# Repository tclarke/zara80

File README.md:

# zara80
A retro computer based on the Z80 and STEbus

See [the hackaday project](https://hackaday.io/project/190621-zara80) for details.

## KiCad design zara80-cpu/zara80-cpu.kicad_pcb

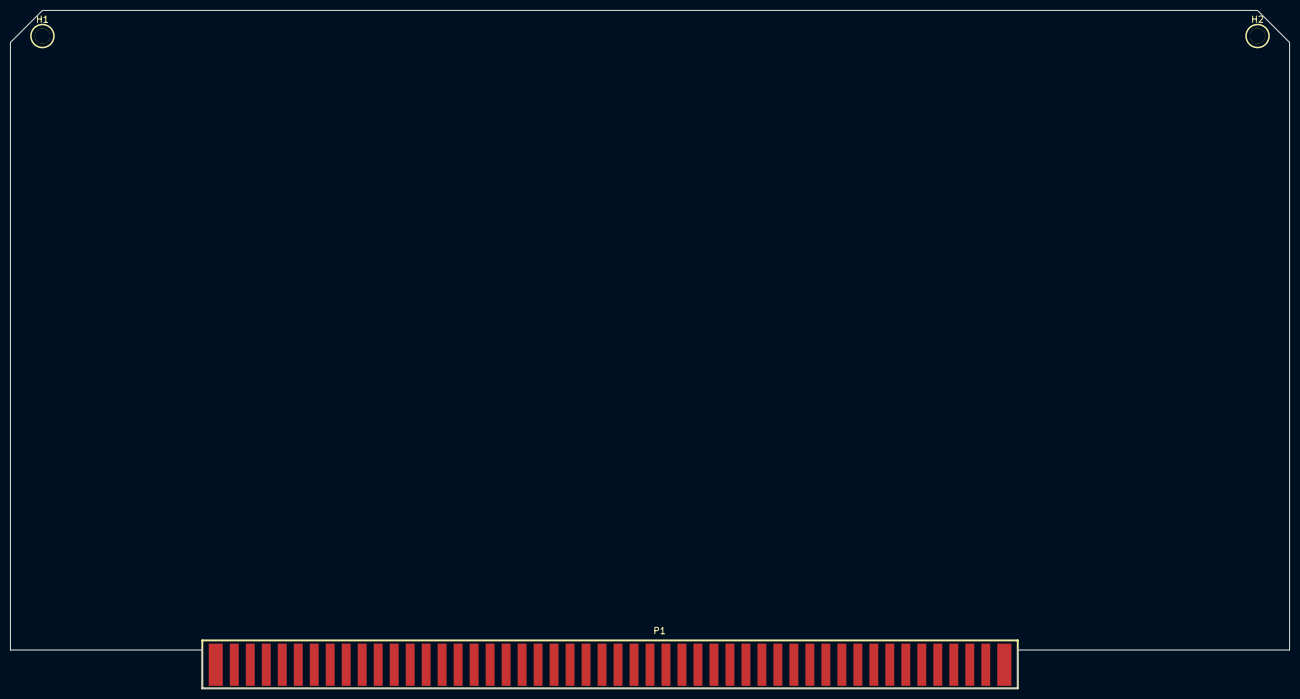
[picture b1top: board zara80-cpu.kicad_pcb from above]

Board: 2 copper layers, 254.0 x 134.6 mm, 3 parts (0 on the bottom side), 2 nets, no tracks yet.

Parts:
H1, H2: Ejector; s100-ejector
P1: S100_MALE

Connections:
/0V: P1.50, P1.100
/+8V: P1.1, P1.51

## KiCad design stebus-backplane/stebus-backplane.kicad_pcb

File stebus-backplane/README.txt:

This is a STEbus backplane with 5 slots and active termination.

It uses an ATX power supply and has options to enable or short
the soft power button for the supply. It can also connect the ATX
+5VSB line to the VSTBY pin on the bus. This allows you to simulate
and test power failures by powering off the soft power button. The VSTBY
acts as a +5V battery. If disabled it connects VSTBY to the normal +5v.

There are no power indicator LEDs since the power supply will typically have
these already.

The active termination uses the sample circuit from the STEbus Standards document.

stebus-backplane.v1.pcbway.gerbers.zip contains the gerbers used to order rev 1
of the board from PCBway who kindly provided free manufacture as a sponsorship
for rev 1.

Most of the parts can be substituted for similar parts. Resistors should be
approximately the same but most can be a few percent off. The (rev 2 and
newer) 2.8v regulator should work fine with any pin compatible regulator. It's
used as a pullup in the termination circuit so it shouldn't pull much current
and the footprint is pretty standard for 2 pin SMD regulators. The DIN
connectors are meant to be interchangable with any DIN41612. They are 2x32 pin
female AC connectors. The Molex is a standard 24-pin ATX connector so other
brands should work fine.

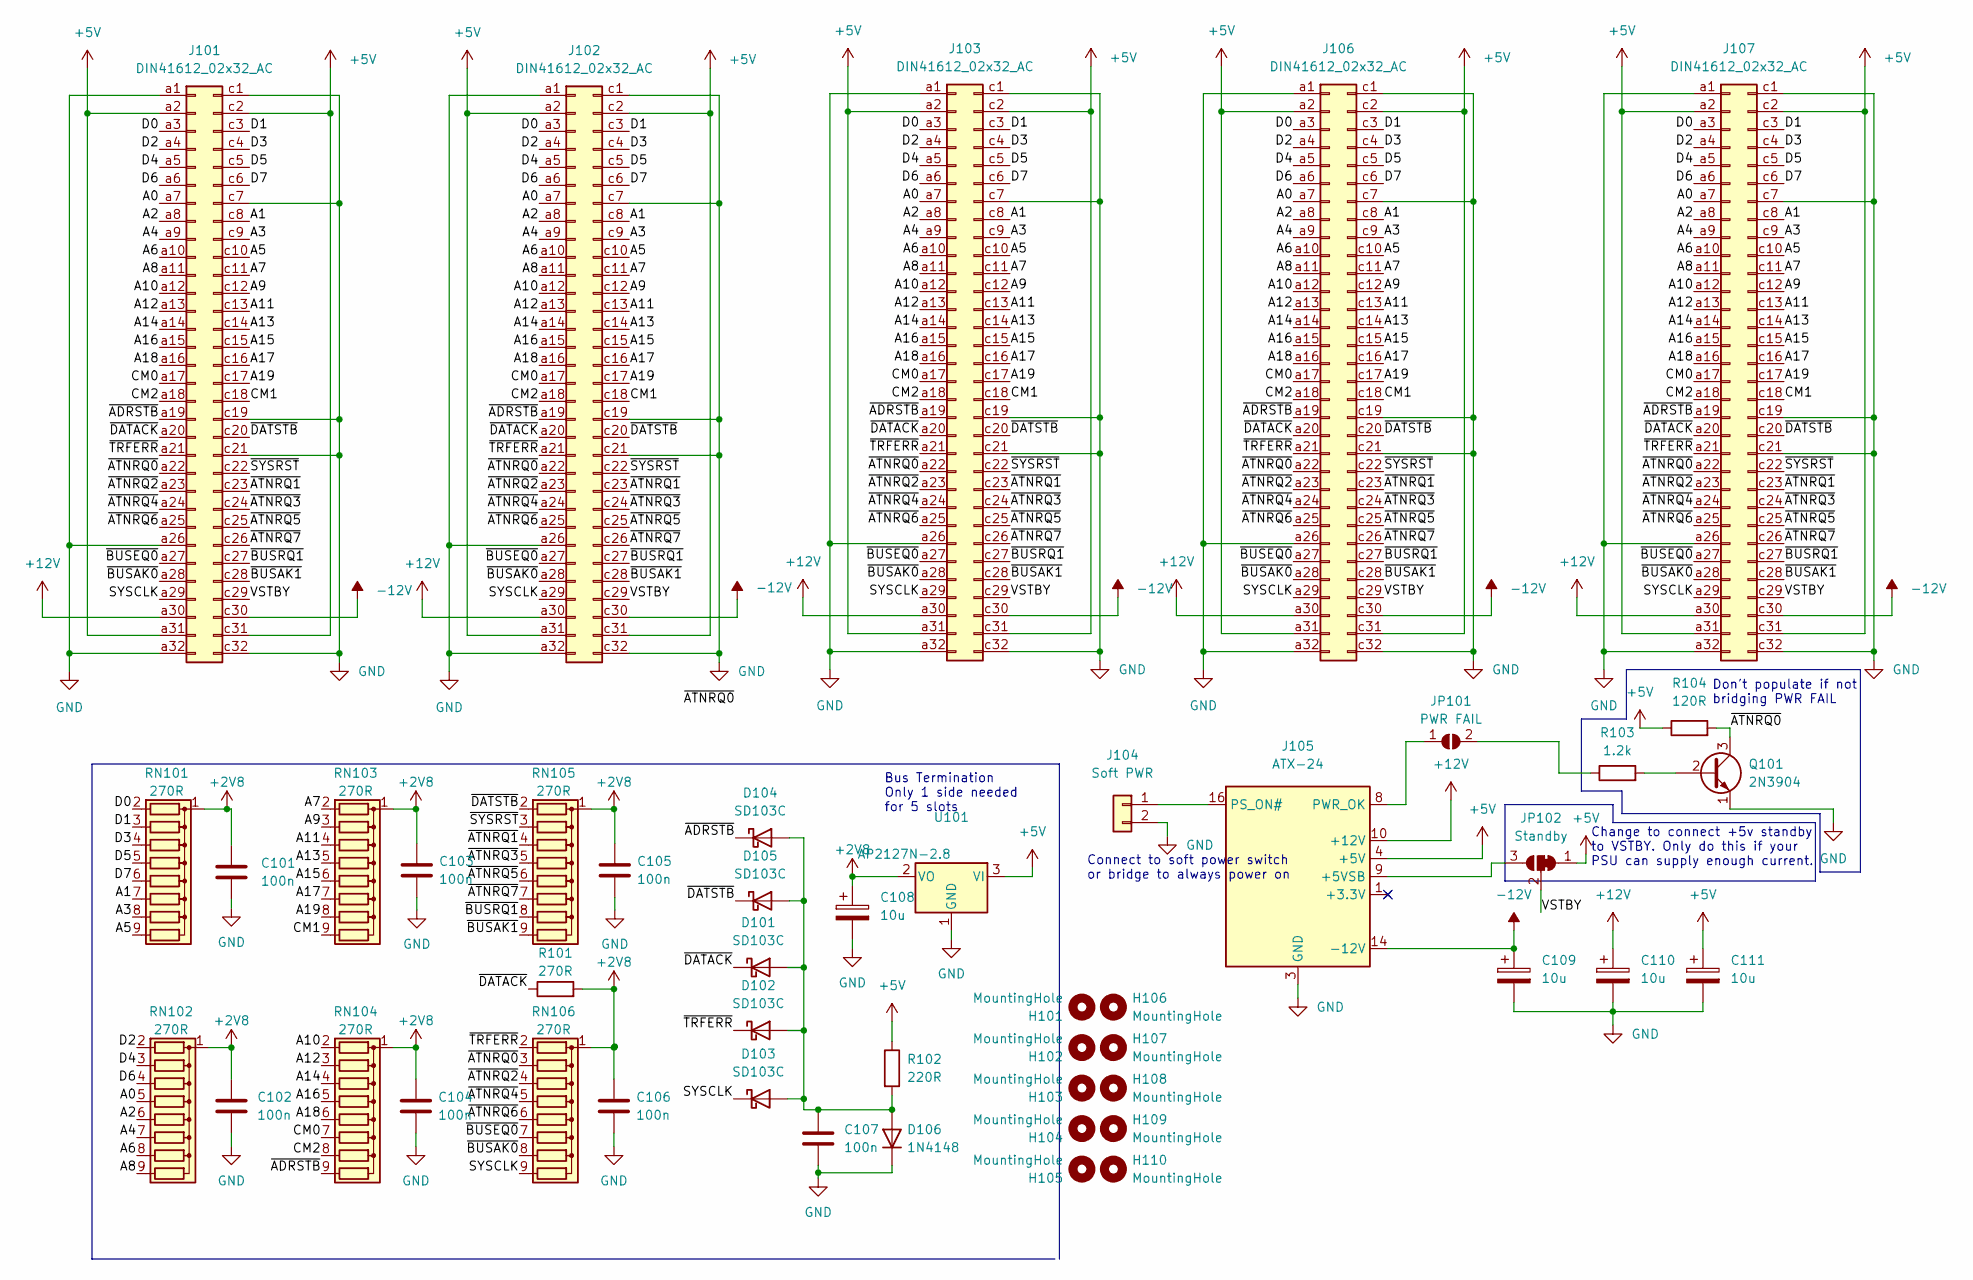
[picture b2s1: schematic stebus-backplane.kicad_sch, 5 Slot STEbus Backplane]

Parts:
C101, C102, C103, C104, C105, C106, C107: 100n; C_0603_1608Metric_Pad1.08x0.95mm_HandSolder; digikey 311-1777-1-ND
C108, C109, C110, C111: 10u; CP_Radial_D6.3mm_P2.50mm; digikey 493-16275-1-ND
D101, D102, D103, D104, D105: SD103C; D_DO-35_SOD27_P7.62mm_Horizontal; digikey SD103CVSCT-ND
D106: 1N4148; D_DO-35_SOD27_P7.62mm_Horizontal; digikey 1N4148FS-ND
H101, H102, H103, H104, H105, H106, H107, H108, H109, H110: MountingHole; MountingHole_3.2mm_M3
J101, J102, J103, J106, J107: DIN41612_02x32_AC; DIN41612_C_2x32_Female_Vertical_THT; digikey 2684-224411-E-ND
J104: Soft PWR; PinHeader_1x02_P2.54mm_Vertical; digikey 1988-1163-ND
J105: ATX-24; Molex_Mini-Fit_Jr_5566-24A2_2x12_P4.20mm_Vertical; digikey WM23811-ND
JP101: PWR FAIL; SolderJumper-2_P1.3mm_Open_RoundedPad1.0x1.5mm
JP102: Standby; SolderJumper-3_P1.3mm_Bridged12_RoundedPad1.0x1.5mm_NumberL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
Q101: 2N3904; TO-92_Inline; digikey 2368-2N3904-ND
R101: 270R; R_Axial_DIN0309_L9.0mm_D3.2mm_P12.70mm_Horizontal; digikey CF18JT270R
R102: 220R; R_Axial_DIN0309_L9.0mm_D3.2mm_P12.70mm_Horizontal; digikey CF18JT220R
R103: 1.2k; R_Axial_DIN0309_L9.0mm_D3.2mm_P12.70mm_Horizontal; digikey CF18JT1K20
R104: 120R; R_Axial_DIN0309_L9.0mm_D3.2mm_P12.70mm_Horizontal; digikey CF18JT120R
RN101, RN102, RN103, RN104, RN105, RN106: 270R; R_Array_SIP9; digikey 4609X-101-271LF-ND
U101: AP2127N-2.8; SOT-23; digikey 31-AP2127N-2.8TRG1CT-ND

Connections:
+2V8: C101.1, C102.1, C103.1, C104.1, C105.1, C106.1, C108.1, R101.2, RN101.1 (common), RN102.1 (common), RN103.1 (common), RN104.1 (common), RN105.1 (common), RN106.1 (common), U101.2 (VO)
+5V: C111.1, J101.a2, J101.a31, J101.c2, J101.c31, J102.a2, J102.a31, J102.c2, J102.c31, J103.a2, J103.a31, J103.c2, J103.c31, J105.4 (+5V), J105.6 (+5V), J105.21 (+5V), J105.22 (+5V), J105.23 (+5V), J106.a2, J106.a31, J106.c2, J106.c31, J107.a2, J107.a31, J107.c2, J107.c31, JP102.1 (A), R102.1, R104.1, U101.3 (VI)
+12V: C110.1, J101.a30, J102.a30, J103.a30, J105.10 (+12V), J105.11 (+12V), J106.a30, J107.a30
-12V: C109.1, J101.c30, J102.c30, J103.c30, J105.14 (-12V), J106.c30, J107.c30
/A0: J101.a7, J102.a7, J103.a7, J106.a7, J107.a7, RN102.5 (R4)
/A1: J101.c8, J102.c8, J103.c8, J106.c8, J107.c8, RN101.7 (R6)
/A2: J101.a8, J102.a8, J103.a8, J106.a8, J107.a8, RN102.6 (R5)
/A3: J101.c9, J102.c9, J103.c9, J106.c9, J107.c9, RN101.8 (R7)
/A4: J101.a9, J102.a9, J103.a9, J106.a9, J107.a9, RN102.7 (R6)
/A5: J101.c10, J102.c10, J103.c10, J106.c10, J107.c10, RN101.9 (R8)
/A6: J101.a10, J102.a10, J103.a10, J106.a10, J107.a10, RN102.8 (R7)
/A7: J101.c11, J102.c11, J103.c11, J106.c11, J107.c11, RN103.2 (R1)
/A8: J101.a11, J102.a11, J103.a11, J106.a11, J107.a11, RN102.9 (R8)
/A9: J101.c12, J102.c12, J103.c12, J106.c12, J107.c12, RN103.3 (R2)
/A10: J101.a12, J102.a12, J103.a12, J106.a12, J107.a12, RN104.2 (R1)
/A11: J101.c13, J102.c13, J103.c13, J106.c13, J107.c13, RN103.4 (R3)
/A12: J101.a13, J102.a13, J103.a13, J106.a13, J107.a13, RN104.3 (R2)
/A13: J101.c14, J102.c14, J103.c14, J106.c14, J107.c14, RN103.5 (R4)
/A14: J101.a14, J102.a14, J103.a14, J106.a14, J107.a14, RN104.4 (R3)
/A15: J101.c15, J102.c15, J103.c15, J106.c15, J107.c15, RN103.6 (R5)
/A16: J101.a15, J102.a15, J103.a15, J106.a15, J107.a15, RN104.5 (R4)
/A17: J101.c16, J102.c16, J103.c16, J106.c16, J107.c16, RN103.7 (R6)
/A18: J101.a16, J102.a16, J103.a16, J106.a16, J107.a16, RN104.6 (R5)
/A19: J101.c17, J102.c17, J103.c17, J106.c17, J107.c17, RN103.8 (R7)
/CM0: J101.a17, J102.a17, J103.a17, J106.a17, J107.a17, RN104.7 (R6)
/CM1: J101.c18, J102.c18, J103.c18, J106.c18, J107.c18, RN103.9 (R8)
/CM2: J101.a18, J102.a18, J103.a18, J106.a18, J107.a18, RN104.8 (R7)
/D0: J101.a3, J102.a3, J103.a3, J106.a3, J107.a3, RN101.2 (R1)
/D1: J101.c3, J102.c3, J103.c3, J106.c3, J107.c3, RN101.3 (R2)
/D2: J101.a4, J102.a4, J103.a4, J106.a4, J107.a4, RN102.2 (R1)
/D3: J101.c4, J102.c4, J103.c4, J106.c4, J107.c4, RN101.4 (R3)
/D4: J101.a5, J102.a5, J103.a5, J106.a5, J107.a5, RN102.3 (R2)
/D5: J101.c5, J102.c5, J103.c5, J106.c5, J107.c5, RN101.5 (R4)
/D6: J101.a6, J102.a6, J103.a6, J106.a6, J107.a6, RN102.4 (R3)
/D7: J101.c6, J102.c6, J103.c6, J106.c6, J107.c6, RN101.6 (R5)
/SYSCLK: D103.1 (K), J101.a29, J102.a29, J103.a29, J106.a29, J107.a29, RN106.9 (R8)
/VSTBY: J101.c29, J102.c29, J103.c29, J106.c29, J107.c29, JP102.2 (C)
/~ADRSTB: D104.1 (K), J101.a19, J102.a19, J103.a19, J106.a19, J107.a19, RN104.9 (R8)
/~ATNRQ0: J101.a22, J102.a22, J103.a22, J106.a22, J107.a22, Q101.3 (C), R104.2, RN106.3 (R2)
/~ATNRQ1: J101.c23, J102.c23, J103.c23, J106.c23, J107.c23, RN105.4 (R3)
/~ATNRQ2: J101.a23, J102.a23, J103.a23, J106.a23, J107.a23, RN106.4 (R3)
/~ATNRQ3: J101.c24, J102.c24, J103.c24, J106.c24, J107.c24, RN105.5 (R4)
/~ATNRQ4: J101.a24, J102.a24, J103.a24, J106.a24, J107.a24, RN106.5 (R4)
/~ATNRQ5: J101.c25, J102.c25, J103.c25, J106.c25, J107.c25, RN105.6 (R5)
/~ATNRQ6: J101.a25, J102.a25, J103.a25, J106.a25, J107.a25, RN106.6 (R5)
/~ATNRQ7: J101.c26, J102.c26, J103.c26, J106.c26, J107.c26, RN105.7 (R6)
/~BUSAK0: J101.a28, J102.a28, J103.a28, J106.a28, J107.a28, RN106.8 (R7)
/~BUSAK1: J101.c28, J102.c28, J103.c28, J106.c28, J107.c28, RN105.9 (R8)
/~BUSEQ0: J101.a27, J102.a27, J103.a27, J106.a27, J107.a27, RN106.7 (R6)
/~BUSRQ1: J101.c27, J102.c27, J103.c27, J106.c27, J107.c27, RN105.8 (R7)
/~DATACK: D101.1 (K), J101.a20, J102.a20, J103.a20, J106.a20, J107.a20, R101.1
/~DATSTB: D105.1 (K), J101.c20, J102.c20, J103.c20, J106.c20, J107.c20, RN105.2 (R1)
/~SYSRST: J101.c22, J102.c22, J103.c22, J106.c22, J107.c22, RN105.3 (R2)
/~TRFERR: D102.1 (K), J101.a21, J102.a21, J103.a21, J106.a21, J107.a21, RN106.2 (R1)
GND: C101.2, C102.2, C103.2, C104.2, C105.2, C106.2, C107.2, C108.2, C109.2, C110.2, C111.2, D106.1 (K), J101.a1, J101.a26, J101.a32, J101.c1, J101.c7, J101.c19, J101.c21, J101.c32, J102.a1, J102.a26, J102.a32, J102.c1, J102.c7, J102.c19, J102.c21, J102.c32, J103.a1, J103.a26, J103.a32, J103.c1, J103.c7, J103.c19, J103.c21, J103.c32, J104.2, J105.3 (GND), J105.5 (GND), J105.7 (GND), J105.15 (GND), J105.17 (GND), J105.18 (GND), J105.19 (GND), J105.24 (GND), J106.a1, J106.a26, J106.a32, J106.c1, J106.c7, J106.c19, J106.c21, J106.c32, J107.a1, J107.a26, J107.a32, J107.c1, J107.c7, J107.c19, J107.c21, J107.c32, Q101.1 (E), U101.1 (GND)
unnamed: C107.1, D101.2 (A), D102.2 (A), D103.2 (A), D104.2 (A), D105.2 (A), D106.2 (A), R102.2
unnamed: J104.1, J105.16 (PS_ON#)
unnamed: J105.8 (PWR_OK), JP101.1 (A)
unnamed: J105.9 (+5VSB), JP102.3 (B)
unnamed: JP101.2 (B), R103.1
unnamed: Q101.2 (B), R103.2

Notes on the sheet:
Change to connect +5v standby to VSTBY. Only do this if your PSU can supply enough current.
Connect to soft power switch or bridge to always power on
Bus Termination Only 1 side needed for 5 slots
Don't populate if not bridging PWR FAIL

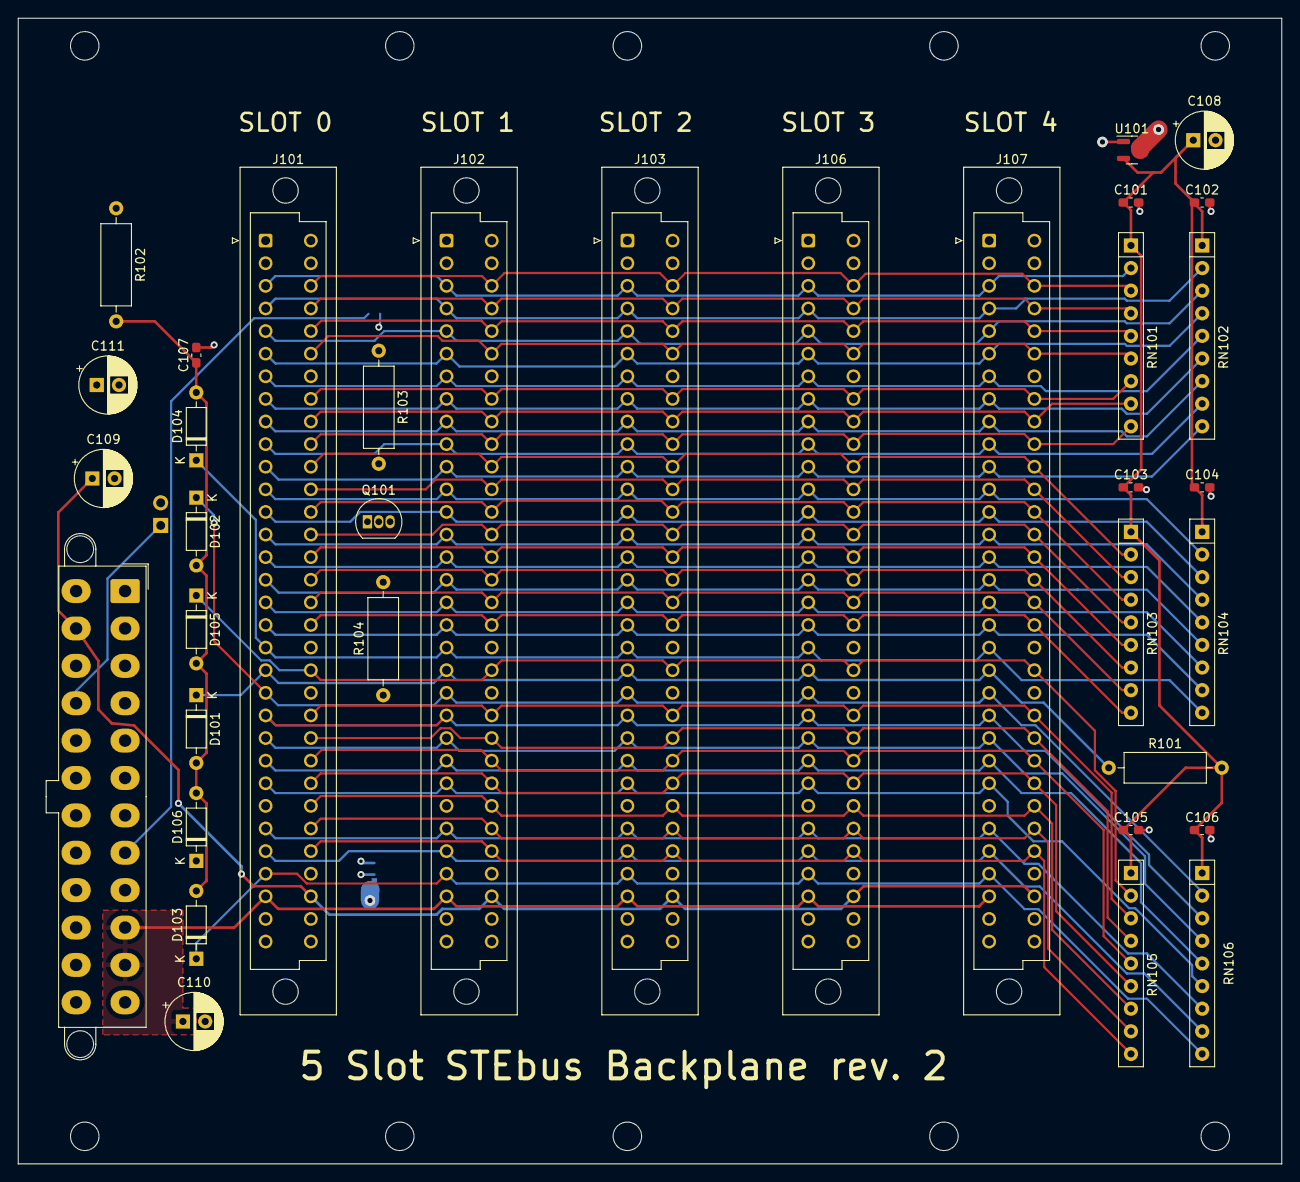
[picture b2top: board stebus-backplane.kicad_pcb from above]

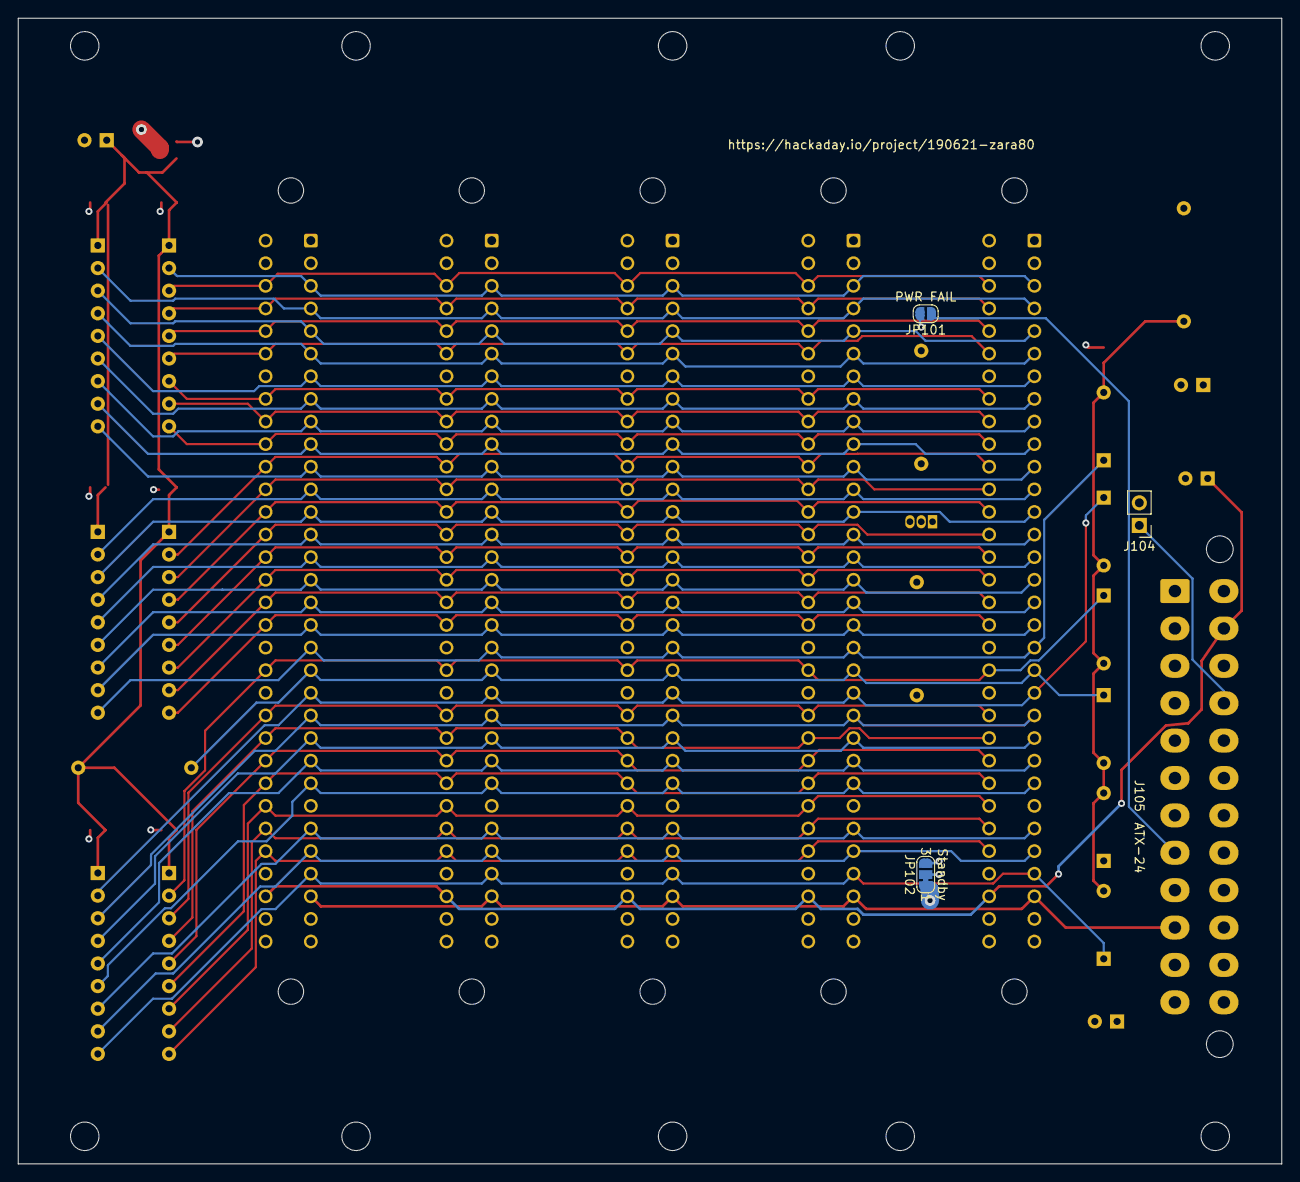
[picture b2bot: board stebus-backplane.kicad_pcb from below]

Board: 4 copper layers, 141.9 x 128.7 mm, 48 parts (3 on the bottom side), 61 nets.

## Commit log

2023-04-30 STEbus 5x backplane rev 1 with PCBWay gerbers.
2023-04-30 Create LICENSE.solderpad
    Add license info. This project is licensed under the Solderpad License v2.1
2023-04-30 Add rev1 plots
2023-04-30 Add index for docs.
2023-04-30 add missing files to docs
2023-04-30 Fix typo
2023-05-01 Added IEEE-1000 spec
2023-05-12 Some documentation updates and a change to set rev1/ as the plot directory in the pro file.
2023-05-30 Update errate and assembly instructions for rev 1
2023-05-30 Update backplane readme
2023-05-30 Add digikey part number of interactive bom
2023-07-17 multiple in-progress items
